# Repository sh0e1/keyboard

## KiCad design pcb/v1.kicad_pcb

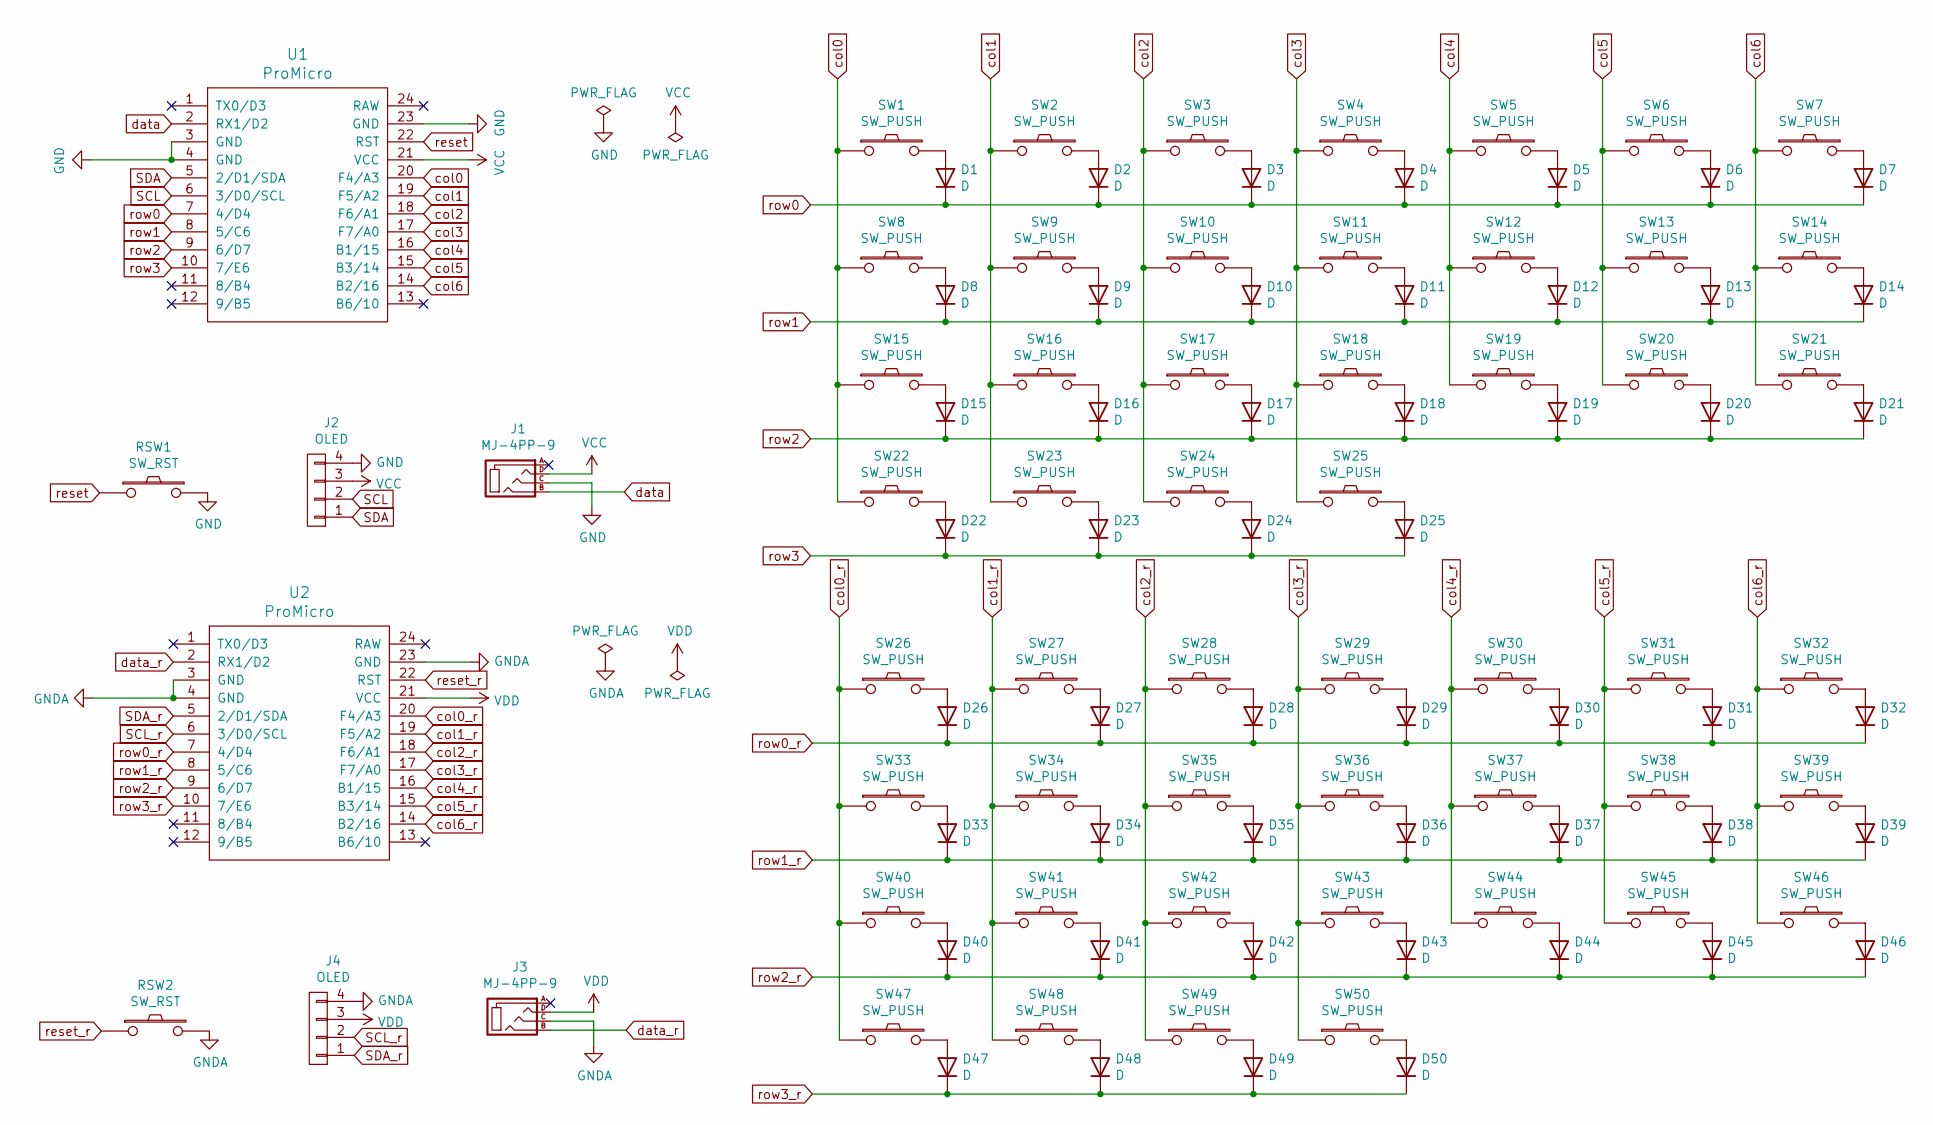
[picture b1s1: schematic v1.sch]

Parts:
D1, D2, D3, D4, D5, D6, D7, D8, D9, D10, D11, D12, D13, D14, D15, D16, D17, D18, D19, D20, D21, D22, D23, D24, D25, D26, D27, D28, D29, D30, D31, D32, D33, D34, D35, D36, D37, D38, D39, D40, D41, D42, D43, D44, D45, D46, D47, D48, D49, D50: D; D3_SMD_v2
J1, J3: MJ-4PP-9; MJ-4PP-9_1side
J2, J4: OLED; OLED_1side
RSW1, RSW2: SW_RST; ResetSW_1side
SW1, SW2, SW3, SW4, SW5, SW6, SW7, SW8, SW9, SW10, SW11, SW12, SW13, SW14, SW16, SW17, SW18, SW19, SW20, SW21, SW23, SW24, SW25, SW26, SW27, SW28, SW29, SW30, SW31, SW32, SW33, SW34, SW35, SW36, SW37, SW38, SW39, SW41, SW42, SW43, SW44, SW45, SW46, SW48, SW49, SW50: SW_PUSH; CherryMX_Hotswap
SW15, SW22, SW40, SW47: SW_PUSH; CherryMX_Hotswap_1.5u
U1, U2: ProMicro; ProMicro_v3

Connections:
GND: J1.C, J2.4, RSW1.2, U1.3 (GND), U1.4 (GND), U1.23 (GND)
GNDA: J3.C, J4.4, RSW2.2, U2.3 (GND), U2.4 (GND), U2.23 (GND)
unnamed: D1.2 (A), SW1.2
unnamed: D2.2 (A), SW2.2
unnamed: D3.2 (A), SW3.2
unnamed: D4.2 (A), SW4.2
unnamed: D5.2 (A), SW5.2
unnamed: D6.2 (A), SW6.2
unnamed: D7.2 (A), SW7.2
unnamed: D8.2 (A), SW8.2
unnamed: D9.2 (A), SW9.2
unnamed: D10.2 (A), SW10.2
unnamed: D11.2 (A), SW11.2
unnamed: D12.2 (A), SW12.2
unnamed: D13.2 (A), SW13.2
unnamed: D14.2 (A), SW14.2
unnamed: D15.2 (A), SW15.2
unnamed: D16.2 (A), SW16.2
unnamed: D17.2 (A), SW17.2
unnamed: D18.2 (A), SW18.2
unnamed: D19.2 (A), SW19.2
unnamed: D20.2 (A), SW20.2
unnamed: D21.2 (A), SW21.2
unnamed: D22.2 (A), SW22.2
unnamed: D23.2 (A), SW23.2
unnamed: D24.2 (A), SW24.2
unnamed: D25.2 (A), SW25.2
unnamed: D26.2 (A), SW26.2
unnamed: D27.2 (A), SW27.2
unnamed: D28.2 (A), SW28.2
unnamed: D29.2 (A), SW29.2
unnamed: D30.2 (A), SW30.2
unnamed: D31.2 (A), SW31.2
unnamed: D32.2 (A), SW32.2
unnamed: D33.2 (A), SW33.2
unnamed: D34.2 (A), SW34.2
unnamed: D35.2 (A), SW35.2
unnamed: D36.2 (A), SW36.2
unnamed: D37.2 (A), SW37.2
unnamed: D38.2 (A), SW38.2
unnamed: D39.2 (A), SW39.2
unnamed: D40.2 (A), SW40.2
unnamed: D41.2 (A), SW41.2
unnamed: D42.2 (A), SW42.2
unnamed: D43.2 (A), SW43.2
unnamed: D44.2 (A), SW44.2
unnamed: D45.2 (A), SW45.2
unnamed: D46.2 (A), SW46.2
unnamed: D47.2 (A), SW47.2
unnamed: D48.2 (A), SW48.2
unnamed: D49.2 (A), SW49.2
unnamed: D50.2 (A), SW50.2
SCL: J2.2, U1.6 (3/D0/SCL)
SCL_r: J4.2, U2.6 (3/D0/SCL)
SDA: J2.1, U1.5 (2/D1/SDA)
SDA_r: J4.1, U2.5 (2/D1/SDA)
VCC: J1.D, J2.3, U1.21 (VCC)
VDD: J3.D, J4.3, U2.21 (VCC)
col0: SW1.1, SW8.1, SW15.1, SW22.1, U1.20 (F4/A3)
col0_r: SW26.1, SW33.1, SW40.1, SW47.1, U2.20 (F4/A3)
col1: SW2.1, SW9.1, SW16.1, SW23.1, U1.19 (F5/A2)
col1_r: SW27.1, SW34.1, SW41.1, SW48.1, U2.19 (F5/A2)
col2: SW3.1, SW10.1, SW17.1, SW24.1, U1.18 (F6/A1)
col2_r: SW28.1, SW35.1, SW42.1, SW49.1, U2.18 (F6/A1)
col3: SW4.1, SW11.1, SW18.1, SW25.1, U1.17 (F7/A0)
col3_r: SW29.1, SW36.1, SW43.1, SW50.1, U2.17 (F7/A0)
col4: SW5.1, SW12.1, SW19.1, U1.16 (B1/15)
col4_r: SW30.1, SW37.1, SW44.1, U2.16 (B1/15)
col5: SW6.1, SW13.1, SW20.1, U1.15 (B3/14)
col5_r: SW31.1, SW38.1, SW45.1, U2.15 (B3/14)
col6: SW7.1, SW14.1, SW21.1, U1.14 (B2/16)
col6_r: SW32.1, SW39.1, SW46.1, U2.14 (B2/16)
data: J1.B, U1.2 (RX1/D2)
data_r: J3.B, U2.2 (RX1/D2)
reset: RSW1.1, U1.22 (RST)
reset_r: RSW2.1, U2.22 (RST)
row0: D1.1 (K), D2.1 (K), D3.1 (K), D4.1 (K), D5.1 (K), D6.1 (K), D7.1 (K), U1.7 (4/D4)
row0_r: D26.1 (K), D27.1 (K), D28.1 (K), D29.1 (K), D30.1 (K), D31.1 (K), D32.1 (K), U2.7 (4/D4)
row1: D8.1 (K), D9.1 (K), D10.1 (K), D11.1 (K), D12.1 (K), D13.1 (K), D14.1 (K), U1.8 (5/C6)
row1_r: D33.1 (K), D34.1 (K), D35.1 (K), D36.1 (K), D37.1 (K), D38.1 (K), D39.1 (K), U2.8 (5/C6)
row2: D15.1 (K), D16.1 (K), D17.1 (K), D18.1 (K), D19.1 (K), D20.1 (K), D21.1 (K), U1.9 (6/D7)
row2_r: D40.1 (K), D41.1 (K), D42.1 (K), D43.1 (K), D44.1 (K), D45.1 (K), D46.1 (K), U2.9 (6/D7)
row3: D22.1 (K), D23.1 (K), D24.1 (K), D25.1 (K), U1.10 (7/E6)
row3_r: D47.1 (K), D48.1 (K), D49.1 (K), D50.1 (K), U2.10 (7/E6)

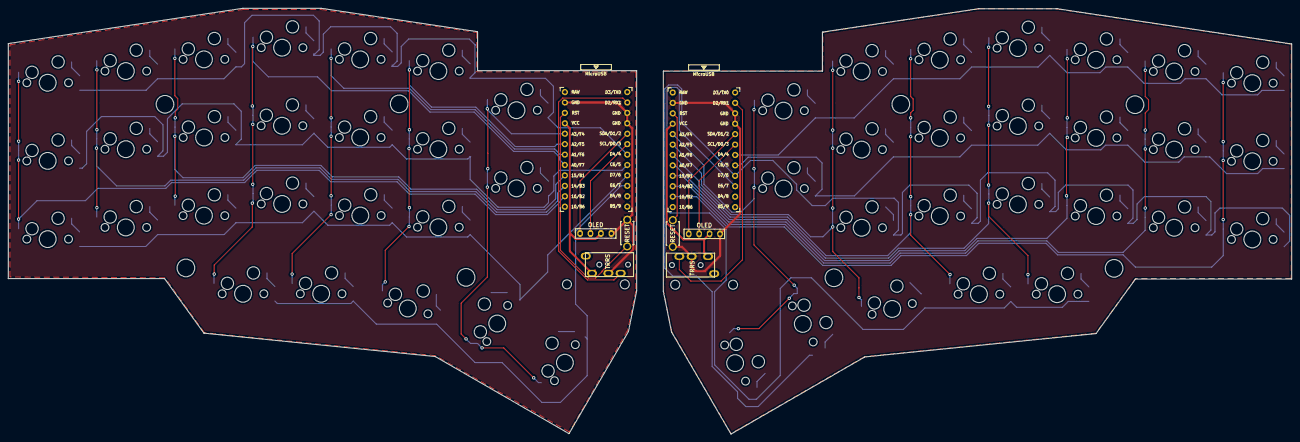
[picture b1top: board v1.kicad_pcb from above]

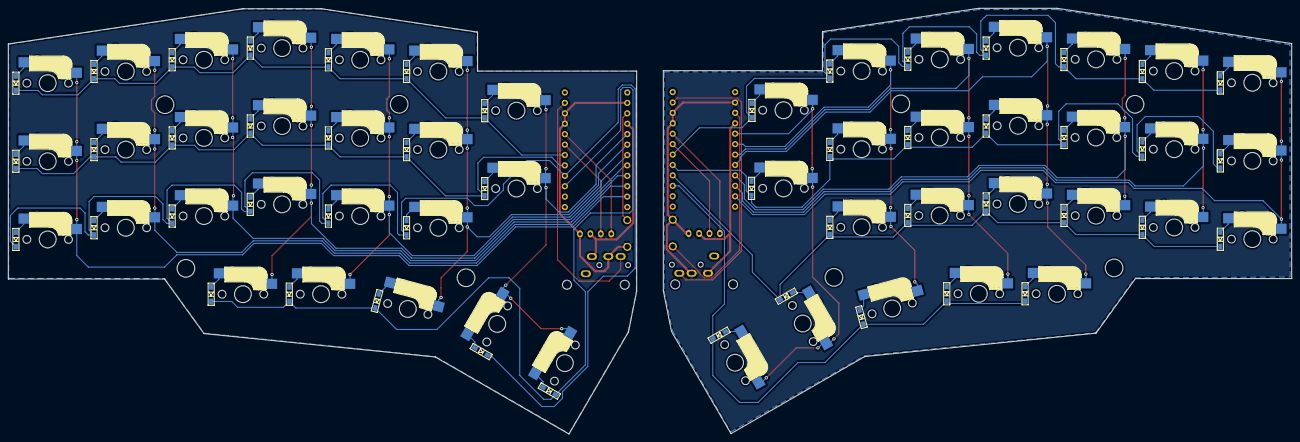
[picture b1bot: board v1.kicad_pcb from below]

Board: 2 copper layers, 312.9 x 103.8 mm, 120 parts (56 on the bottom side), 84 nets.

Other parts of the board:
Ref**: Val**; M2_HOLE_v2
Ref**#2, Ref**#3, Ref**#4, Ref**#5, Ref**#6, Ref**#7, Ref**#8, Ref**#9, Ref**#10, Ref**#11, Ref**#12: Val**; M2_HOLE_v2

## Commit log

2021-07-22 :tada: Initial Commit
2021-07-25 :sparkles: Add: KiCad files
2021-07-31 :+1: Update
2021-08-01 :sparkles: Add: case.dwg
2021-08-01 :sparkles: Add: pcb directory
2021-08-01 :wastebasket: Remove: unnecessary files
